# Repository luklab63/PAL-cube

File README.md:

# PAL V2 

## electronics 

* ESP32 C6 dev-module
* 2x SG90 servo moteurs 
* SH1106 0.94" OLED screen 
* power switch 
* small battery bank 
* used usb cable 
* PCB 
* 2 LEDs + 2x 220ohm resistors 

## The PCB 

it is a simple PCB that holds the ESP32 the battery connector and the screen and servo connectors. it is 70 x 60 mm. two 3mm LEDs 

## firmware

### APK

the apk was designed in MIT app inventor using the BLE library and by revers engineering the BLE-controller project on github.

the app is used to control the servo motors and the face that is shown
### The code 

the code is also based on the BLE-controller project however i have modified a lot to add the U2G8 library to control the screen

the faces are stored in the bitmap.h file. to get the bitmaps for each face you need to convert your image to XBM and than open it with a text editor 

## The shoulder mount and 3D prints
this mount is modeled for my shoulder, there are cutouts on the arms that rap around the shoulder to loop a custom made belt so the whole assembly is stable.the neck and head are screwed to this mount via some heatset inserts and the whole assembly is pretty stable once installed properly 

pictures and gifs coming soon.

the ESP-32 and PCB fit into a small boxed attached to the belt the power switch and LEDS will be visible? i will try to get some acrilic cut to fit as a lid for said box.

## final product 

the final product i intend to make is a shoulder mounted PAL that is battery powered. 

## funding required

i am pretty autonomous for electronics and coding however funding is needed for 3D printing filament and to print out the PCB.

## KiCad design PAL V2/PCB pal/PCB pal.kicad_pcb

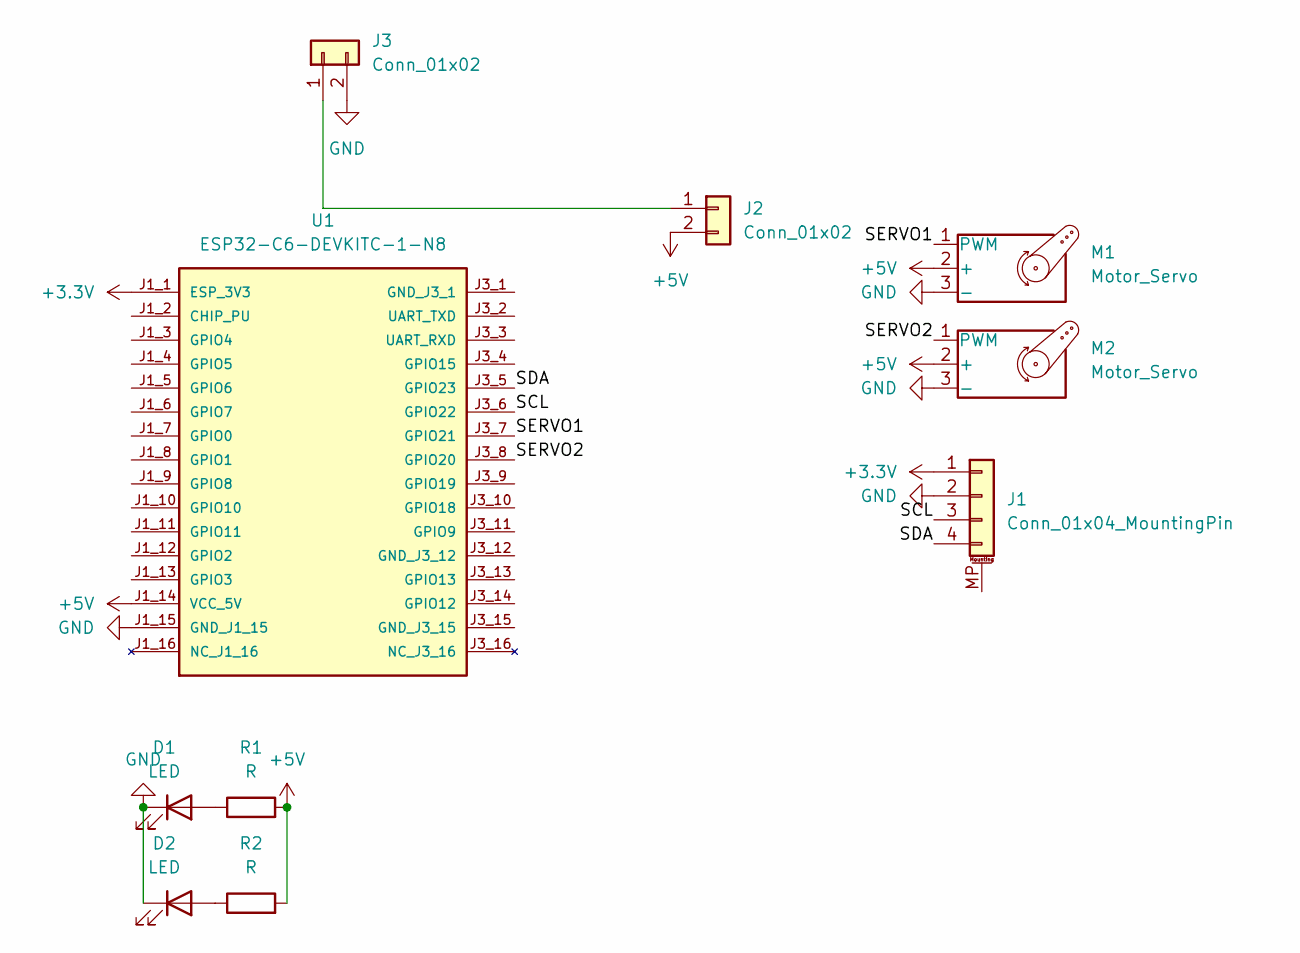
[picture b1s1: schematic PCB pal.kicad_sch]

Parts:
D1, D2: LED; LED_D3.0mm
J1: Conn_01x04_MountingPin; PinHeader_1x04_P2.54mm_Vertical
J2: Conn_01x02; PinHeader_1x02_P2.54mm_Vertical
J3: Conn_01x02; BatteryTERMINAL
M1, M2: Motor_Servo; PinHeader_1x03_P2.54mm_Vertical
R1, R2: R; R_Axial_DIN0207_L6.3mm_D2.5mm_P10.16mm_Horizontal
U1: ESP32-C6-DEVKITC-1-N8; MODULE_ESP32-C6-DEVKITC-1-N8; PARTREV 1.3

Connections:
+3.3V: J1.1, U1.J1_1 (ESP_3V3)
+5V: J2.2, M1.2 (+), M2.2 (+), R1.2, R2.2, U1.J1_14 (VCC_5V)
/SCL: J1.3, U1.J3_6 (GPIO22)
/SDA: J1.4, U1.J3_5 (GPIO23)
/SERVO1: M1.1 (PWM), U1.J3_7 (GPIO21)
/SERVO2: M2.1 (PWM), U1.J3_8 (GPIO20)
GND: D1.1 (K), D2.1 (K), J1.2, J3.2, M1.3 (-), M2.3 (-), U1.J1_15 (GND_J1_15)
unnamed: D1.2 (A), R1.1
unnamed: D2.2 (A), R2.1
unnamed: J2.1, J3.1

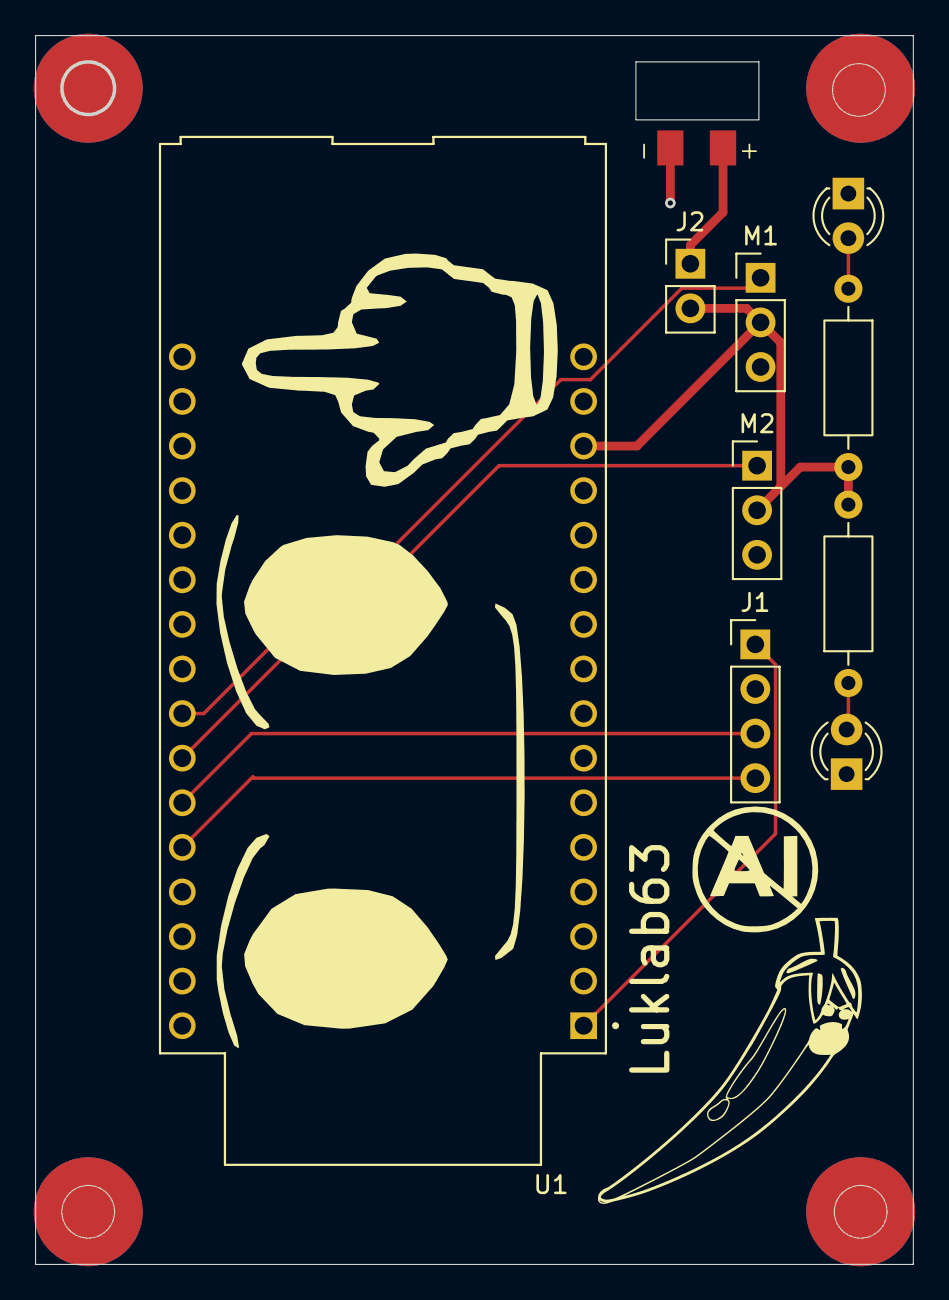
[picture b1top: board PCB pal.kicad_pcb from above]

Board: 2 copper layers, 50.0 x 70.0 mm, 10 parts (0 on the bottom side), 10 nets.

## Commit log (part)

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2026-03-17 first comit
2026-03-22 3D model
2026-03-22 folders
2026-03-22 readme
2026-03-22 cat pal
2026-03-22 better 3D models
2026-03-22 better cat faces
